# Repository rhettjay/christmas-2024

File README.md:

# Christmas Tree 2024

The below image demonstrates the correct orientation and placement of the diodes and resistors.
Follow the diagram on the back of the pcb. With the shorter leg (cathode) going into the square hole from the front of the pcb and the long leg (anode) going into the round hole.
After the led is soldered in place you can safely snip the legs.

solder the battery clip by adding solder to both of the square pads on either side of the large circle such that it will fit in the following orientation:

I unfortunately only had 68 Ohm resistors which are slightly too resistive and the LEDs at the top show a little dull.
If you would like them a little more brilliant you can either replace the resisistors with 62 Ohm resistors or bypass one or both of the resistors by soldering a wire directly to the first trace.
Be aware if you do this the LEDs can short out, or it will drain the battery earlier because the resistance in the circuit will be too low.

The on position of the switch is in the position marked on the board. Make sure to solder the switch with the three legs fitting into the solder pads.

Alternatively you can just enjoy the ornament for what it is without any leds.

Merry Christmas!

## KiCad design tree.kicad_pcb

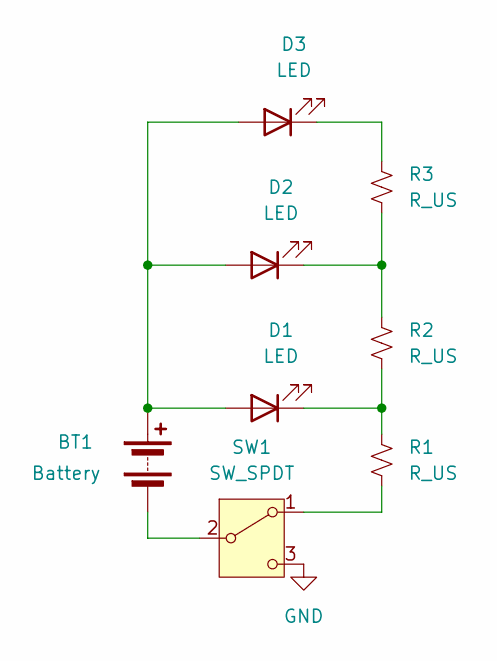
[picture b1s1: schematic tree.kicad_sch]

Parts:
BT1: Battery; BatteryHolder_Multicomp_BC-2001_1x2032
D1, D2, D3: LED; LED_D1.8mm_W3.3mm_H2.4mm
R1, R2, R3: R_US; R_0805_2012Metric_Pad1.20x1.40mm_HandSolder
SW1: SW_SPDT; SW_SPDT_PCM12C03

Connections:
GND: SW1.3 (C)
unnamed: BT1.1 (+), D1.2 (A), D2.2 (A), D3.2 (A)
unnamed: BT1.2 (-), SW1.2 (B)
unnamed: D1.1 (K), R1.1, R2.2
unnamed: D2.1 (K), R2.1, R3.2
unnamed: D3.1 (K), R3.1
unnamed: R1.2, SW1.1 (A)

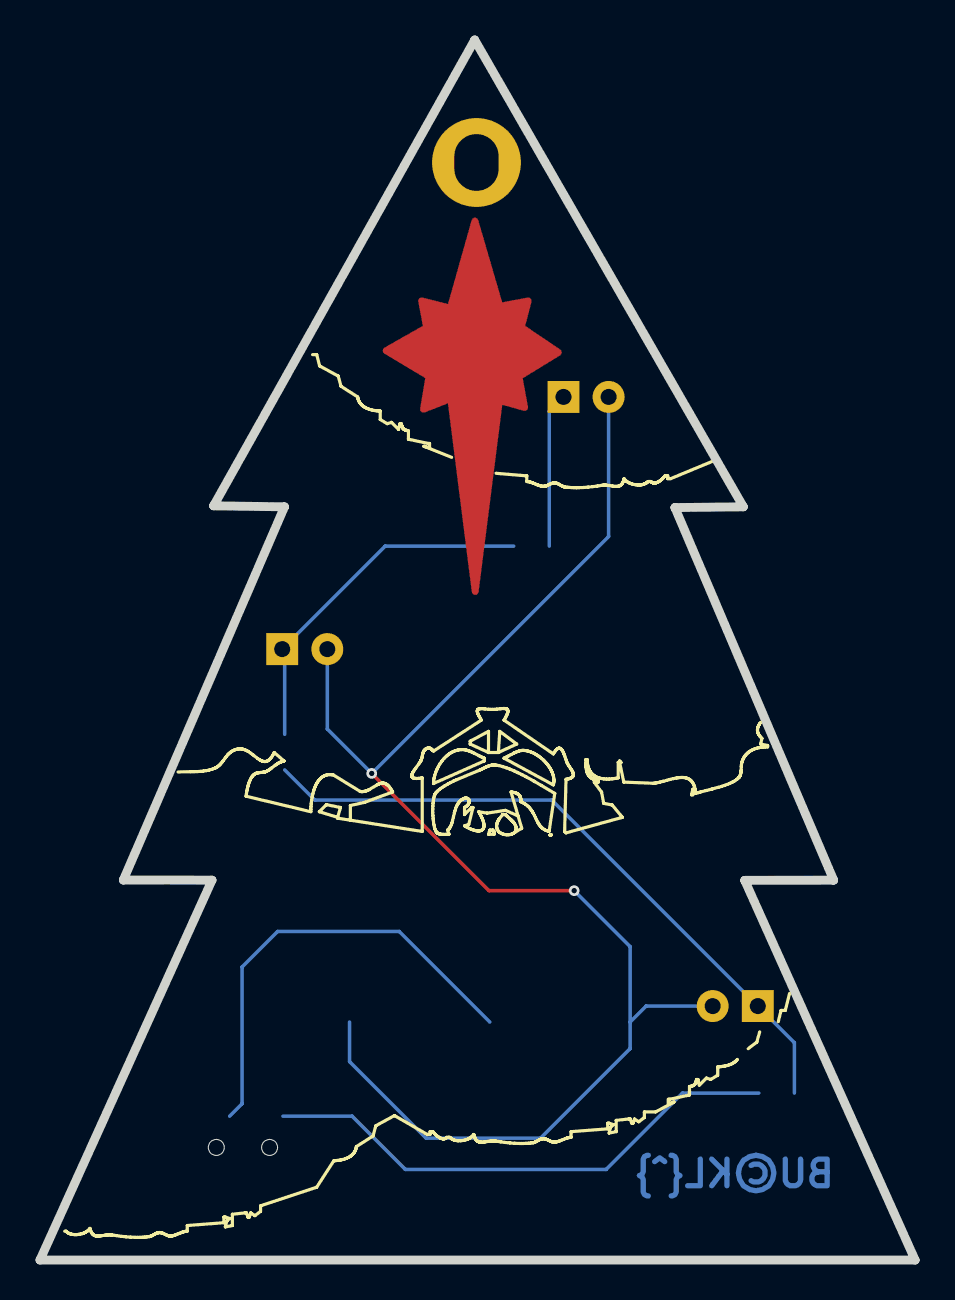
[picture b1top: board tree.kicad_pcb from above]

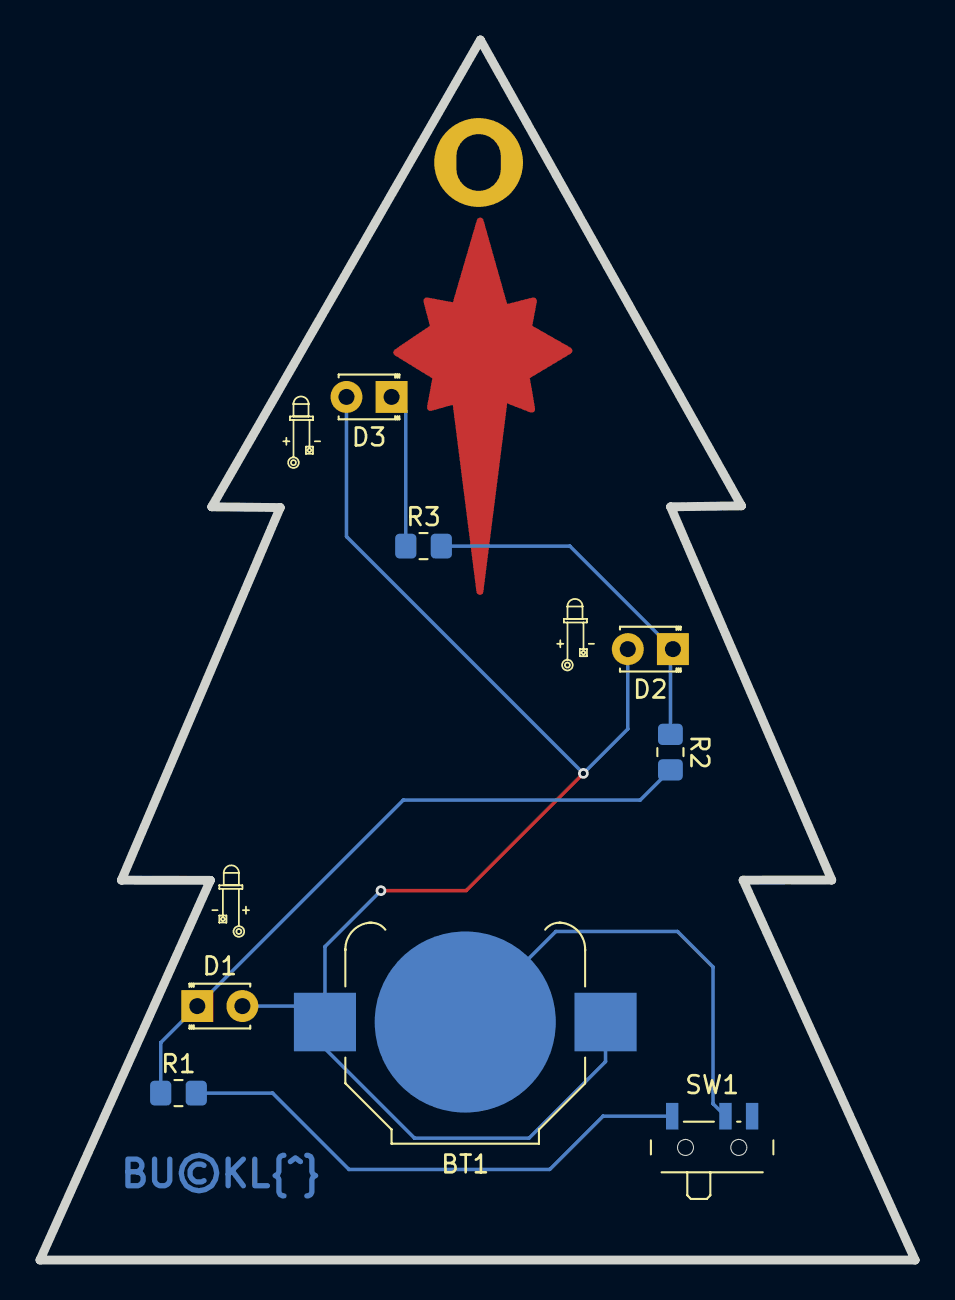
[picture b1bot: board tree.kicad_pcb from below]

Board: 2 copper layers, 49.3 x 68.7 mm, 8 parts (8 on the bottom side), 6 nets.

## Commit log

2024-12-17 pcb files
2024-12-17 tree images
2024-12-17 Merry Christmas
2024-12-19 battery image
2024-12-19 battery
